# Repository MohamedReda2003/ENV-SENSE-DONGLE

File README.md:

# Batarang ESP32-S3 IoT Badge 🦇⚡

Une carte de développement IoT personnalisée en forme de **Batarang**, conçue autour du microcontrôleur **ESP32-S3-MINI-1** et équipée d'un capteur environnemental **BME280**.

## 📌 Aperçu du Projet

Ce projet combine une forme de PCB personnalisée (*Batarang*) avec une architecture matérielle complète pour des applications IoT embarquées (station météo portable, badge connecté, nœud de capteurs Wi-Fi/Bluetooth). Il intègre les meilleures pratiques de conception électronique (DFM, protection ESD, découplage localisé et intégrité de signal).

## 🚀 Caractéristiques Techniques

| Composant | Référence / Spécification | Description | 
| ----- | ----- | ----- | 
| **Microcontrôleur** | **ESP32-S3-MINI-1** | Wi-Fi $2.4\text{ GHz}$, Bluetooth 5 (LE), Antenne PCB intégrée, $8\text{ MB}$ Flash, $512\text{ KB}$ SRAM | 
| **Capteur Environnemental** | **BME280** | Mesure de température, humidité relative et pression atmosphérique (I2C) | 
| **Alimentation / LDO** | **AP2112K-3.3** | Régulateur LDO $3.3\text{ V}$ / $600\text{ mA}$ à faible chute de tension (*Low Dropout*) | 
| **Connectique** | **USB-C (16 broches)** | Interface d'alimentation $5\text{ V}$ et de programmation USB native | 
| **Protection ESD** | **USBLC6-2SC6** | Protection contre les décharges électrostatiques sur les lignes de données USB | 
| **Boutons** | 2x Boutons poussoirs | **SW1** (Reset / EN) & **SW2** (Boot / IO0) | 
| **Affichage Signalétique** | LED SMD / THT | **D1** (LED utilisateur reliée à `IO4`) | 

## 📐 Architecture Générale du Schématique

## 🔍 Explications Détaillées des Blocs du Circuit

### Partie 1 : Interface USB-C & Protection ESD (`J1`, `U1`)

#### Fonctionnement technique :

* **Négociation de Puissance USB-C (`J1`) :** Les broches `CC1` ($A5$) et `CC2` ($B5$) de l'embase USB-C sont chacune tirées à la masse via une résistance dédiée `R1` ($5.1\text{ k}\Omega$) et `R2` ($5.1\text{ k}\Omega$). Ce pont informe la source d'alimentation (hôte USB ou chargeur) que le module est un périphérique récepteur (*Sink/UFP*) et déclenche la délivrance du rail $V_{\text{BUS}}$ ($5\text{ V}$).

* **Compatibilité et Réversibilité :** Les broches de données $A6$/$B6$ (`USB_D+`) et $A7$/$B7$ (`USB_D-`) sont reliées deux à deux sur le connecteur pour garantir la transmission des données USB $2.0$ quel que soit le sens d'insertion du câble.

* **Protection contre Surtensions Transitoires (`U1` - USBLC6-2SC6) :** Les lignes de données passent obligatoirement à travers le composant de protection ESD avant d'atteindre le microcontrôleur. En cas de décharge électrostatique lors du branchement à chaud (*Hot-plug*), les diodes TVS internes dérivent la surtension vers le plan de masse (`GND`), protégeant l'étage logique de l'ESP32.

### Partie 2 : Étage d'Alimentation & Régulation LDO (`U2`)

#### Fonctionnement technique :

* **Régulation de Tension (`U2` - AP2112K-3.3) :** Le composant convertit la tension d'entrée $V_{\text{BUS}}$ ($5\text{ V}$) issue de l'USB en une tension fixe et régulée de $3.3\text{ V}$ (`+3V3`) capable de fournir jusqu'à $600\text{ mA}$.

* **Activation Automatique :** La broche `EN` (broche 3) est directement câblée à $V_{\text{BUS}}$, ce qui garantit le démarrage immédiat du régulateur dès la mise sous tension de la carte.

* **Filtrage Capacitif et Stabilité :**

  * `C1` ($10\ \mu\text{F}$) stabilise la tension d'entrée et absorbe les pics d'appel de courant à la connexion.

  * `C2` ($10\ \mu\text{F}$) fournit une réserve d'énergie locale en sortie pour maintenir la tension stable lors des appels de courant.

  * `C3` ($100\text{ nF}$) filtre les bruits résiduels et perturbations à haute fréquence sur le rail `+3V3`.

### Partie 3 : Capteur Environnemental BME280 (`U3`)

#### Fonctionnement technique :

* **Communication Bus I2C :** Le capteur communique avec le microcontrôleur via les lignes de bus `SDA` (données) et `SCL` (horloge). Les résistances de tirage `R3` ($4.7\text{ k}\Omega$) et `R4` ($4.7\text{ k}\Omega$) tirent les lignes vers `+3V3`, ce qui est requis pour le bus I2C à drain ouvert.

* **Configuration du Mode I2C :** La broche `CSB` (Chip Select) est maintenue au niveau haut (`+3V3`) pour désactiver la fonction SPI et forcer le mode I2C.

* **Adresse I2C Statique :** La broche `SDO` est reliée à la masse (`GND`), fixant l'adresse de bus I2C du composant à **`0x76`** (si elle était reliée à `+3V3`, l'adresse deviendrait `0x77`).

* **Filtrage Alimentation :** Le condensateur `C4` ($100\text{ nF}$) assure le découplage des broches `VDD` et `VDDIO`.

### Partie 4 : Microcontrôleur ESP32-S3 & Periphériques de Contrôle (`U4`)

#### Fonctionnement technique :

* **Cœur de Traitement (`U4` - ESP32-S3-MINI-1) :** Module équipé d'un processeur double cœur $32\text{ bits}$ opérant jusqu'à $240\text{ MHz}$, gérant la communication sans-fil Wi-Fi/BLE et le contrôleur USB matériel natif.

* **Circuit Reset Temporisé (`EN` - Broche 45) :**

  * La résistance de pull-up `R5` ($10\text{ k}\Omega$) reliée à `+3V3` et le condensateur `C5` ($1\ \mu\text{F}$) vers `GND` créent une constante de temps $RC \approx 10\text{ ms}$.

  * Cela maintient l'ESP32 sous Reset pendant le temps nécessaire à la stabilisation complète de l'alimentation $3.3\text{ V}$.

  * Le bouton `SW1` permet un Reset manuel à tout moment.

* **Sélecteur de Mode Boot (`IO0` - Broche 4) :**

  * La ligne `IO0` est tirée au niveau haut par `R6` ($10\text{ k}\Omega$) pour démarrer normalement sur le firmware en mémoire Flash.

  * L'appui sur le bouton `SW2` lors d'un Reset force `IO0` à la masse, basculant l'ESP32 en mode Bootloader/Flashage USB.

* **Découplage Hautes Performances :** Les condensateurs `C7` ($10\ \mu\text{F}$) et `C6` ($100\text{ nF}$) sont placés immédiatement contre la broche `3V3` du module pour absorber les pics de courant générés par le transmetteur radio Wi-Fi.

* **Interface Utilisateur :** La LED `D1` reliée à l'GPIO `IO4` avec sa résistance de limitation `R7` ($200\ \Omega$) sert de témoin visuel ou d'indicateur d'état du programme.

## 🎨 Conception du PCB & Layout DFM

### Choix de Conception :

1. **Forme Personnalisée (`Edge.Cuts`) :** Découpe mécanique sous forme de Batarang.

2. **Gestion des Plans de Cuivre :**

   * **Face Supérieure (`F.Cu`) :** Plan d'alimentation dédié au rail `+3V3`.

   * **Face Inférieure (`B.Cu`) :** Plan de masse continu `GND` assurant un faible retour d'impédance et un bon blindage CEM.

3. **Zone Inoccupée Antenne (`Keepout Area`) :** Zone entièrement dégagée de cuivre, de composants et de plan de masse sous l'antenne méandre du module **ESP32-S3-MINI-1** pour maximiser le rayonnement radio.

## 🖼️ Galerie 3D

| Face Avant (Top View) | Face Arrière (Bottom View) | 
| ----- | ----- | 
|   |   | 

## 📦 Nomenclature des Composants (BOM)

| Désignation | Empreinte / Boîtier | Valeur | Quantité | Rôle | 
| ----- | ----- | ----- | ----- | ----- | 
| **U4** | ESP32-S3-MINI-1 | ESP32-S3 | 1 | Microcontrôleur principal | 
| **U3** | LGA-8 ($2.5 \times 2.5\text{ mm}$) | BME280 | 1 | Capteur Température / Humidité / Pression | 
| **U2** | SOT-23-5 | AP2112K-3.3 | 1 | Régulateur LDO 5V -> 3.3V | 
| **U1** | SOT-23-6 | USBLC6-2SC6 | 1 | Diode de protection ESD USB | 
| **J1** | SMD 16 Pins | USB-C Receptacle | 1 | Connecteur d'alimentation et data USB | 
| **SW1, SW2** | Push Button $6 \times 6\text{ mm}$ | SW_Push | 2 | Boutons Reset (EN) & Boot (IO0) | 
| **D1** | LED 3mm / 1206 | LED | 1 | Témoin lumineux utilisateur sur IO4 | 
| **R1, R2** | 0805 / 0603 | $5.1\text{ k}\Omega$ | 2 | Résistances Pull-down USB CC | 
| **R3, R4** | 0805 / 0603 | $4.7\text{ k}\Omega$ | 2 | Résistances Pull-up Bus I2C | 
| **R5, R6** | 0805 / 0603 | $10\text{ k}\Omega$ | 2 | Résistances Pull-up EN / Boot | 
| **R7** | 0805 / 0603 | $200\ \Omega$ | 1 | Resistance de limitation pour LED D1 | 
| **C1, C2, C7** | 0805 / Radial | $10\ \mu\text{F}$ | 3 | Condensateurs de filtrage et réservoir | 
| **C3, C4, C6** | 0805 / Axial | $100\text{ nF}$ | 3 | Condensateurs de découplage HF | 
| **C5** | 0805 / Axial | $1\ \mu\text{F}$ | 1 | Condensateur de retard Reset | 

## 💻 Flash & Programmation

1. Connectez la carte à votre ordinateur via le câble USB-C.

2. Si le flash automatique ne s'exécute pas automatiquement :

   * Maintenez le bouton **Boot (`SW2`)** enfoncé.

   * Appuyez brièvement sur le bouton **Reset (`SW1`)**.

   * Relâchez le bouton **Boot (`SW2`)** pour placer l'ESP32-S3 en mode *Download*.

3. Transférez votre code via **Arduino IDE** (choisir la carte `ESP32S3 Dev Module`) ou **PlatformIO**.

## 📜 Licence

Ce projet est publié sous licence **MIT**. Vous êtes libre de l'utiliser, le modifier et le distribuer.

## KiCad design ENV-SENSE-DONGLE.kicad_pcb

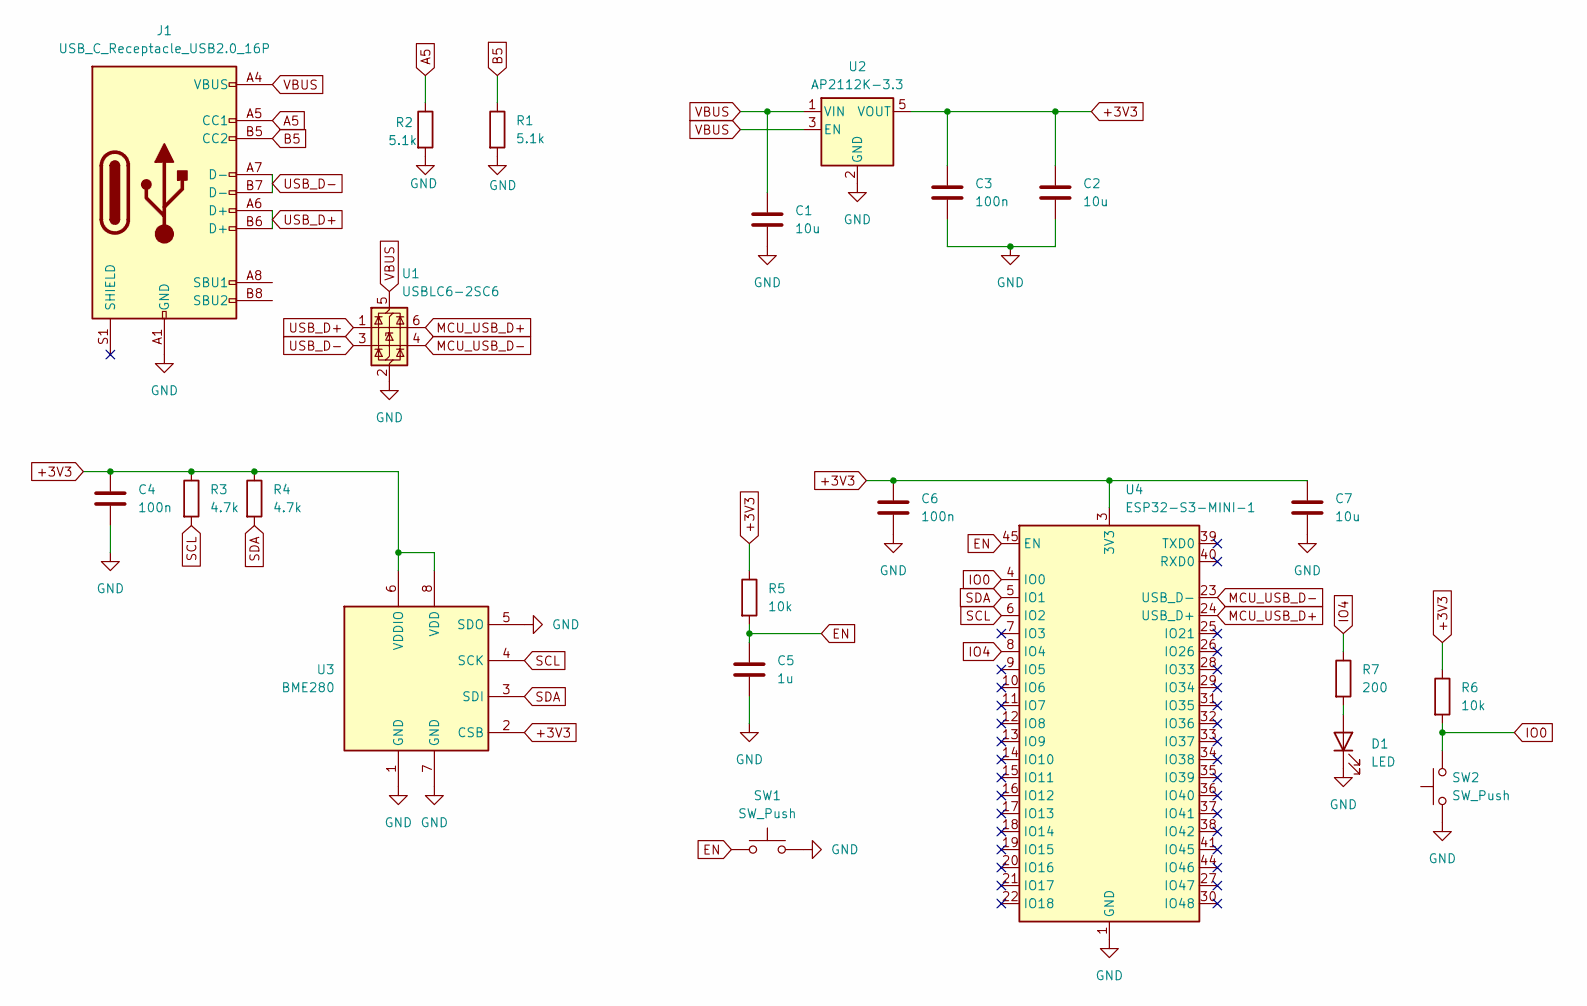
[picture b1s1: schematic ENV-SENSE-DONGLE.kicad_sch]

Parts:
C1, C2, C7: 10u; CP_Axial_L10.0mm_D4.5mm_P15.00mm_Horizontal
C3, C4, C6: 100n; CP_Axial_L10.0mm_D4.5mm_P15.00mm_Horizontal
C5: 1u; CP_Axial_L10.0mm_D4.5mm_P15.00mm_Horizontal
D1: LED; LED_D1.8mm_W1.8mm_H2.4mm_Horizontal_O3.81mm_Z4.9mm
J1: USB_C_Receptacle_USB2.0_16P; USB_C_Receptacle_HRO_TYPE-C-31-M-12
R1, R2: 5.1k; R_Axial_DIN0204_L3.6mm_D1.6mm_P2.54mm_Vertical
R3, R4: 4.7k; R_Axial_DIN0204_L3.6mm_D1.6mm_P2.54mm_Vertical
R5, R6: 10k; R_Axial_DIN0204_L3.6mm_D1.6mm_P2.54mm_Vertical
R7: 200; R_Axial_DIN0204_L3.6mm_D1.6mm_P2.54mm_Vertical
SW1, SW2: SW_Push; SW_PUSH_6mm
U1: USBLC6-2SC6; SOT-23-6
U2: AP2112K-3.3; SOT-23-5
U3: BME280; Bosch_LGA-8_2.5x2.5mm_P0.65mm_ClockwisePinNumbering
U4: ESP32-S3-MINI-1; ESP32-S2-MINI-1

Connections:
+3V3: C2.1, C3.1, C4.1, C6.1, C7.1, R3.1, R4.1, R5.1, R6.1, U2.5 (VOUT), U3.2 (CSB), U3.6 (VDDIO), U3.8 (VDD), U4.3 (3V3)
A5: J1.A5 (CC1), R2.1
B5: J1.B5 (CC2), R1.1
EN: C5.1, R5.2, SW1.1, U4.45 (EN)
GND: C1.2, C2.2, C3.2, C4.2, C5.2, C6.2, C7.2, D1.1 (K), J1.A1 (GND), J1.A12 (GND), J1.B1 (GND), J1.B12 (GND), R1.2, R2.2, SW1.2, SW2.1, U1.2 (GND), U2.2 (GND), U3.1 (GND), U3.5 (SDO), U3.7 (GND), U4.1 (GND), U4.2 (GND), U4.42 (GND), U4.43 (GND), U4.46 (GND), U4.47 (GND), U4.48 (GND), U4.49 (GND), U4.50 (GND), U4.51 (GND), U4.52 (GND), U4.53 (GND), U4.54 (GND), U4.55 (GND), U4.56 (GND), U4.57 (GND), U4.58 (GND), U4.59 (GND), U4.60 (GND), U4.61 (GND), U4.62 (GND), U4.63 (GND), U4.64 (GND), U4.65 (GND)
IO0: R6.2, SW2.2, U4.4 (IO0)
IO4: R7.1, U4.8 (IO4)
MCU_USB_D+: U1.6 (I/O1), U4.24 (USB_D+)
MCU_USB_D-: U1.4 (I/O2), U4.23 (USB_D-)
unnamed: D1.2 (A), R7.2
SCL: R3.2, U3.4 (SCK), U4.6 (IO2)
SDA: R4.2, U3.3 (SDI), U4.5 (IO1)
USB_D+: J1.A6 (D+), J1.B6 (D+), U1.1 (I/O1)
USB_D-: J1.A7 (D-), J1.B7 (D-), U1.3 (I/O2)
VBUS: C1.1, J1.A4 (VBUS), J1.A9 (VBUS), J1.B4 (VBUS), J1.B9 (VBUS), U1.5 (VBUS), U2.1 (VIN), U2.3 (EN)

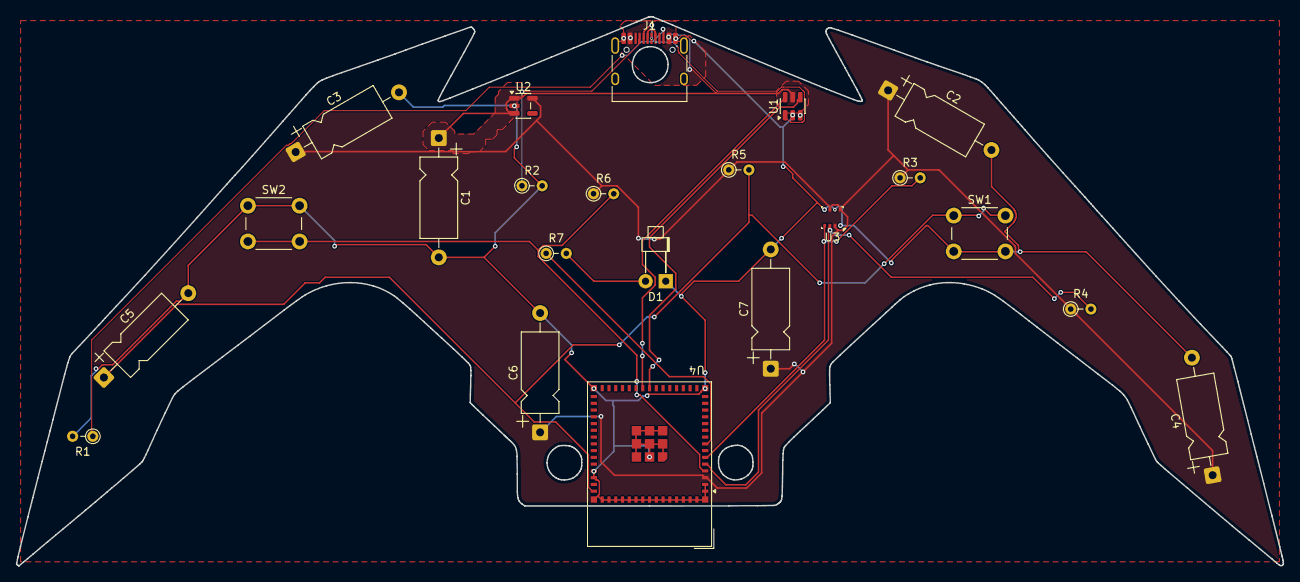
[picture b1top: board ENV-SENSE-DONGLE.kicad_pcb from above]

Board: 2 copper layers, 159.3 x 69.0 mm, 22 parts (0 on the bottom side), 15 nets.
